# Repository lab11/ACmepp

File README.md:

AC Power Meters
===============

This repository contains code and hardware for a set of AC power meters.

ACme++
------

ACme++ is an updated version of the [ACme](http://acme.eecs.berkeley.edu) device.
The major change is a switch from the Epic platform (MSP430F1611 and CC2420) to
the CC2538 system on chip. Other changes include putting the relay on the phase
wire (instead of neutral) and a smaller AC-DC power supply.

While ACme++ is a wireless power meter in its own right, it was designed to be 
a prototype for the ultra-space-constrained PowerCube device.

PowerCube
---------

PowerCube is a one cubic inch power meter. It is designed to unobtrusively fit
on a power strip. This requires using six PCBs arranged in a cube with very
strategically placed components.

Software
--------

Software for the ACme++ is written on top of ContikiOS.

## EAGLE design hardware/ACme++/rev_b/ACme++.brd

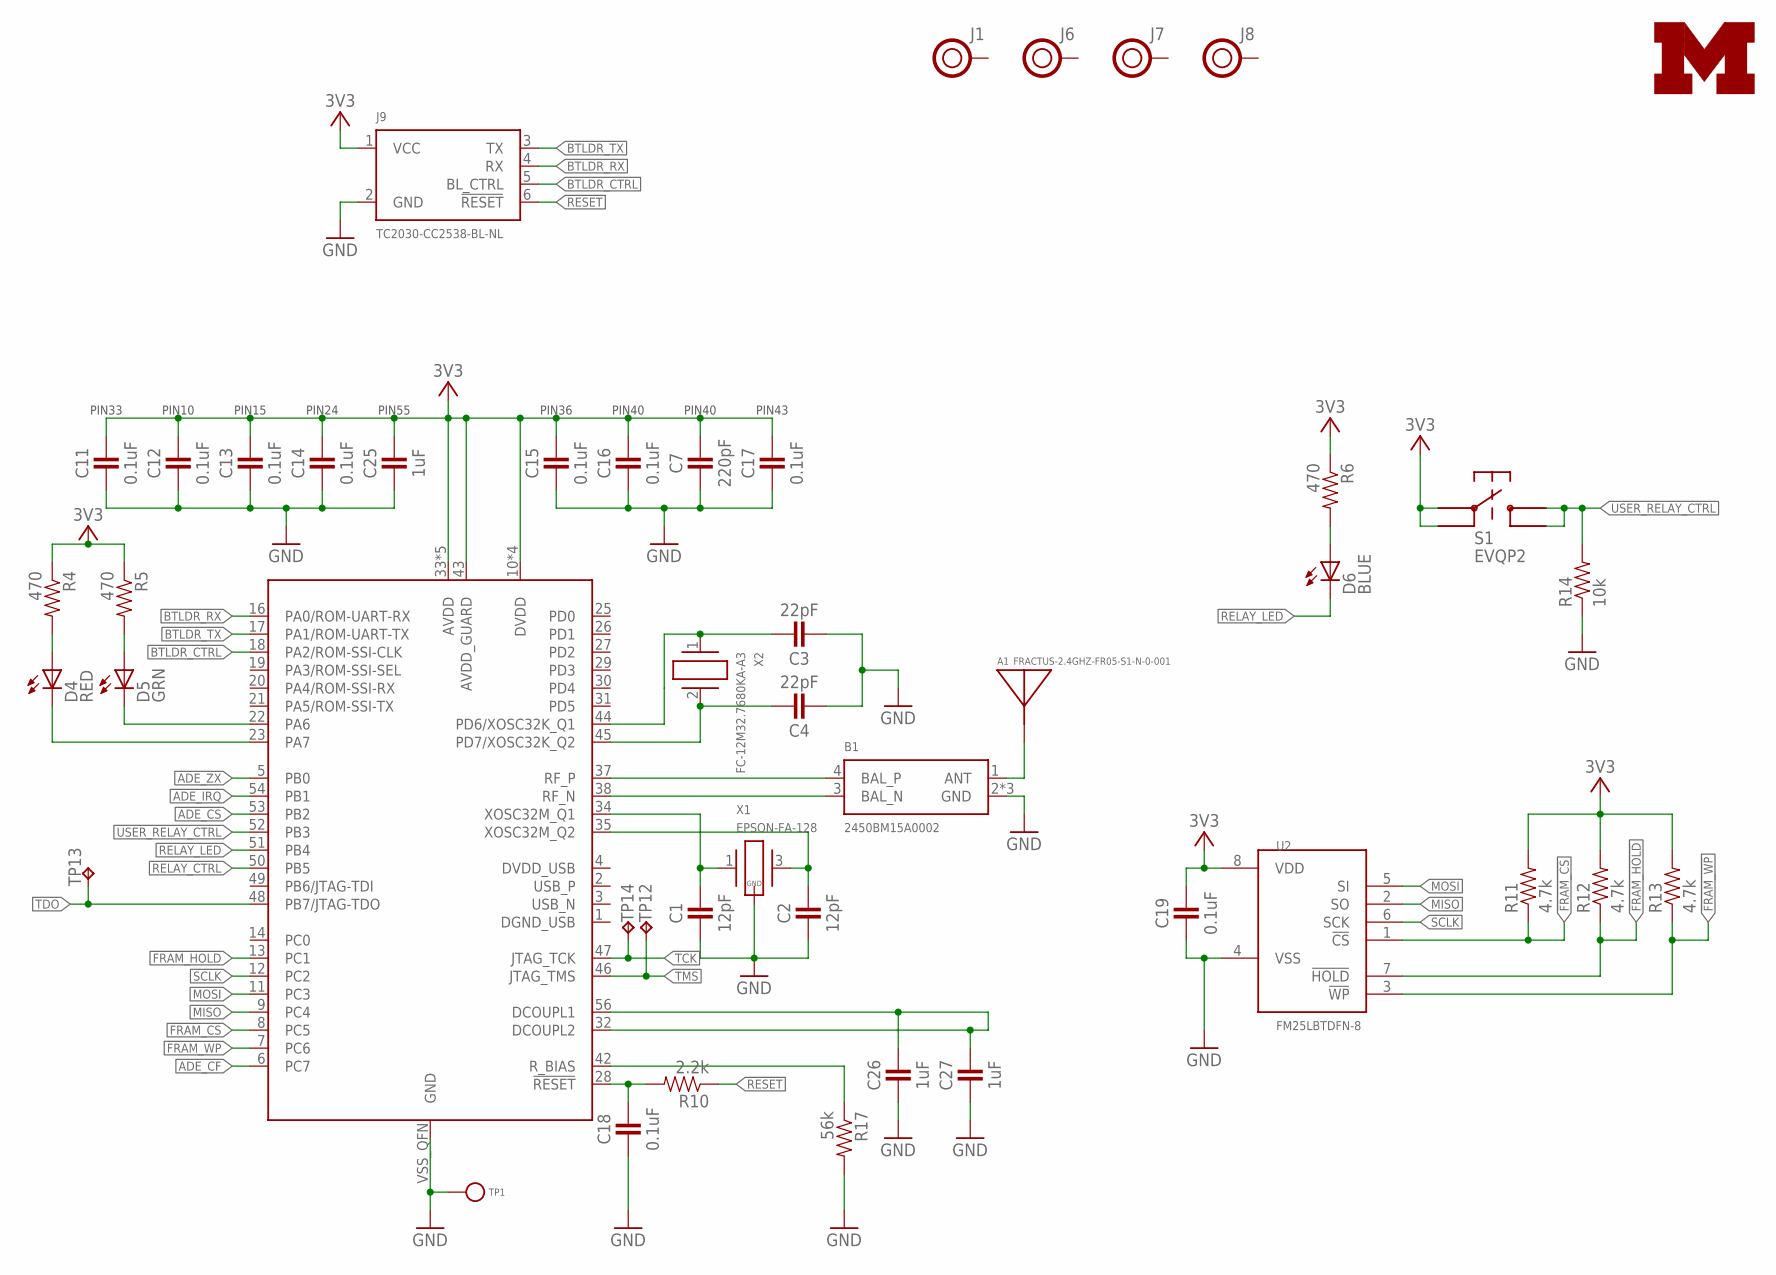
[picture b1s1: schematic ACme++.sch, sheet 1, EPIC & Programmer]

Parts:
A1: FRACTUS-2.4GHZ-FR05-S1-N-0-001; FRACTUS-ANTENNA-FR05-S1-N-0-001
B1: 2450BM15A0002; 2450BM
C1, C2: 12pF; 0402_CAP; DIGIKEY 445-1236-1-ND
C3, C4: 22pF; 0402_CAP; DIGIKEY 490-5868-1-ND
C7: 220pF; 0402_CAP; DIGIKEY 445-1251-1-ND
C11, C12, C13, C14, C15, C16, C17, C18, C19: 0.1uF; 0402_CAP; DIGIKEY 445-1265-1-ND
C25, C26, C27: 1uF; 0402_CAP; DIGIKEY 445-4998-1-ND
D4: RED; LED-0603; DIGIKEY 160-1835-1-ND
D5: GRN; LED-0603; DIGIKEY 160-1834-1-ND
D6: BLUE; LED-0603; DIGIKEY 160-1837-1-ND
J1, J6, J7, J8: HOLE; HOLE-0.125
J9: TC2030-CC2538-BL-NL; TC2030-IDC-NL
R4, R5, R6: 470; 0402_RES; DIGIKEY RHM470BHCT-ND
R10: 2.2k; 0402_RES; DIGIKEY RHM2.2KCECT-ND
R11, R12, R13: 4.7k; 0402_RES; DIGIKEY RHM4.7KCECT-ND
R14: 10k; 0603-RES; DIGIKEY RHM10.0KCFCT-ND
R17: 56k; 0402_RES; DIGIKEY RHM56KBHCT-ND
S1: EVQP2; DIGIKEY P11084SCT-ND
TP1: TEST_POINT_0.040IN; TESTPOINT_0.040IN
TP12, TP13, TP14: TPTP09SQ; TP09SQ
U1: CC2538; S-PVQFN-N56
U2: FM25LBTDFN-8; TDFN-8; DIGIKEY FM25L04B-DGRA-ND
U$3: UMICH_SOLID_MEDIUM; UMICH_SOLID_200MIL
X1: EPSON-FA-128; FA-128; DIGIKEY SER3800CT-ND
X2: FC-12M32.7680KA-A3; FC-12M

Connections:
3V3: C7.1, C11.1, C12.1, C13.1, C14.1, C15.1, C16.1, C17.1, C19.1, C25.1, J9.1 (VCC), R4.1, R5.1, R6.1, R11.2, R12.2, R13.2, S1.P$1, S1.P$3, U1.10 (DVDD), U1.15 (DVDD), U1.24 (DVDD), U1.33 (AVDD), U1.36 (AVDD), U1.39 (AVDD), U1.40 (AVDD), U1.41 (AVDD), U1.43 (AVDD_GUARD), U1.55 (DVDD), U2.8 (VDD); also elsewhere on the board
!ADE_CS: U1.53 (PB2); also elsewhere on the board
!ADE_IRQ: U1.54 (PB1); also elsewhere on the board
!FRAM_CS: R11.1, U1.8 (PC5), U2.1 (!CS)
!FRAM_HOLD: R12.1, U1.13 (PC1), U2.7 (!HOLD)
!FRAM_WP: R13.1, U1.7 (PC6), U2.3 (!WP)
!RESET: J9.6 (!RESET), R10.1
ADE_CF: U1.6 (PC7); also elsewhere on the board
ADE_ZX: U1.5 (PB0); also elsewhere on the board
ANTENNA: A1.1, B1.1 (ANT)
BTLDR_CTRL: J9.5 (BL_CTRL), U1.18 (PA2/ROM-SSI-CLK)
BTLDR_RX: J9.4 (RX), U1.16 (PA0/ROM-UART-RX)
BTLDR_TX: J9.3 (TX), U1.17 (PA1/ROM-UART-TX)
GND: B1.2 (GND), B1.5 (GND), B1.6 (GND), C1.2, C2.2, C3.2, C4.2, C7.2, C11.2, C12.2, C13.2, C14.2, C15.2, C16.2, C17.2, C18.2, C19.2, C25.2, C26.2, C27.2, J9.2 (GND), R14.1, R17.2, TP1.TESTPOINT, U1.VSS_QFN (GND), U2.4 (VSS), X1.2 (GND), X1.4 (GND); also elsewhere on the board
GREEN_LED: D5.C, U1.22 (PA6)
MISO: U1.9 (PC4), U2.2 (SO); also elsewhere on the board
MOSI: U1.11 (PC3), U2.5 (SI); also elsewhere on the board
unnamed: C26.1, C27.1, U1.32 (DCOUPL2), U1.56 (DCOUPL1)
unnamed: C18.1, R10.2, U1.28 (!RESET)
unnamed: C4.1, U1.45 (PD7/XOSC32K_Q2), X2.2
unnamed: C3.1, U1.44 (PD6/XOSC32K_Q1), X2.1
unnamed: R17.1, U1.42 (R_BIAS)
unnamed: C1.1, U1.34 (XOSC32M_Q1), X1.1
unnamed: C2.1, U1.35 (XOSC32M_Q2), X1.3 (2)
unnamed: D6.A, R6.2
unnamed: D4.A, R4.2
unnamed: D5.A, R5.2
RED_LED: D4.C, U1.23 (PA7)
RELAY_CTRL: U1.50 (PB5); also elsewhere on the board
RELAY_LED: D6.C, U1.51 (PB4)
RF_N: B1.3 (BAL_N), U1.38 (RF_N)
RF_P: B1.4 (BAL_P), U1.37 (RF_P)
SCLK: U1.12 (PC2), U2.6 (SCK); also elsewhere on the board
TCK: TP14.TP, U1.47 (JTAG_TCK)
TDO: TP13.TP, U1.48 (PB7/JTAG-TDO)
TMS: TP12.TP, U1.46 (JTAG_TMS)
USER_RELAY_CTRL: R14.2, S1.P$2, S1.P$4, U1.52 (PB3)

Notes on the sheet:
PIN10
PIN15
PIN24
PIN55
PIN33
PIN36
PIN40
PIN43

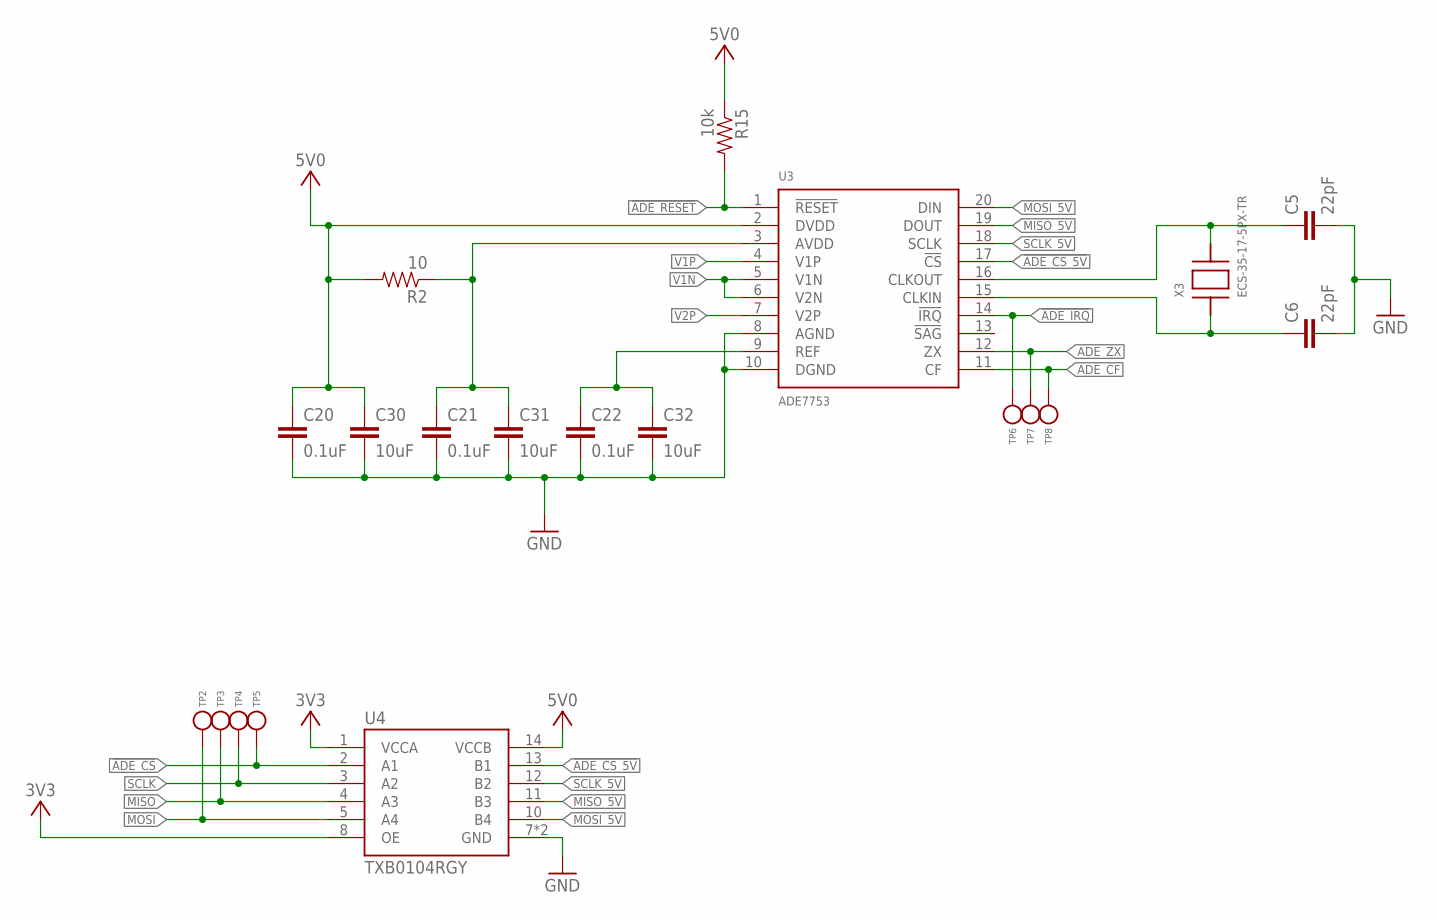
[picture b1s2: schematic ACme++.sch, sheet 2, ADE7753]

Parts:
C5, C6: 22pF; 0603-CAP; DIGIKEY 445-1273-1-ND
C20, C21, C22: 0.1uF; 0603-CAP; DIGIKEY 445-1316-1-ND
C30, C31, C32: 10uF; 0603-CAP; DIGIKEY 1276-1119-1-ND
R2: 10; 0603-RES; DIGIKEY RHM10.0CFCT-ND
R15: 10k; 0603-RES; DIGIKEY RHM10.0KCFCT-ND
TP2, TP3, TP4, TP5, TP6, TP7, TP8: TEST_POINT_0.040IN; TESTPOINT_0.040IN
U3: ADE7753; SSOP-20; MOUSER 584-ADE7753ARSZR
U4: TXB0104RGY; S-PVQFN-N14
X3: ECS-35-17-5PX-TR; CSM-7X

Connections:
3V3: U4.1 (VCCA), U4.8 (OE); also elsewhere on the board
5V0: C20.1, C30.1, R2.2, R15.1, U3.2 (DVDD), U4.14 (VCCB); also elsewhere on the board
!ADE_CS: TP5.TESTPOINT, U4.2 (A1); also elsewhere on the board
!ADE_CS_5V: U3.17 (!CS), U4.13 (B1)
!ADE_IRQ: TP6.TESTPOINT, U3.14 (!IRQ); also elsewhere on the board
!ADE_RESET: R15.2, U3.1 (!RESET)
ADE_AVDD: C21.1, C31.1, R2.1, U3.3 (AVDD)
ADE_CF: TP8.TESTPOINT, U3.11 (CF); also elsewhere on the board
ADE_ZX: TP7.TESTPOINT, U3.12 (ZX); also elsewhere on the board
GND: C5.2, C6.2, C20.2, C21.2, C22.2, C30.2, C31.2, C32.2, U3.8 (AGND), U3.10 (DGND), U4.7 (GND), U4.THERMALPAD (GND); also elsewhere on the board
MISO: TP3.TESTPOINT, U4.4 (A3); also elsewhere on the board
MISO_5V: U3.19 (DOUT), U4.11 (B3)
MOSI: TP2.TESTPOINT, U4.5 (A4); also elsewhere on the board
MOSI_5V: U3.20 (DIN), U4.10 (B4)
unnamed: C6.1, U3.15 (CLKIN), X3.1
unnamed: C22.1, C32.1, U3.9 (REF)
unnamed: C5.1, U3.16 (CLKOUT), X3.2
SCLK: TP4.TESTPOINT, U4.3 (A2); also elsewhere on the board
SCLK_5V: U3.18 (SCLK), U4.12 (B2)
V1N: U3.5 (V1N), U3.6 (V2N); also elsewhere on the board
V1P: U3.4 (V1P); also elsewhere on the board
V2P: U3.7 (V2P); also elsewhere on the board

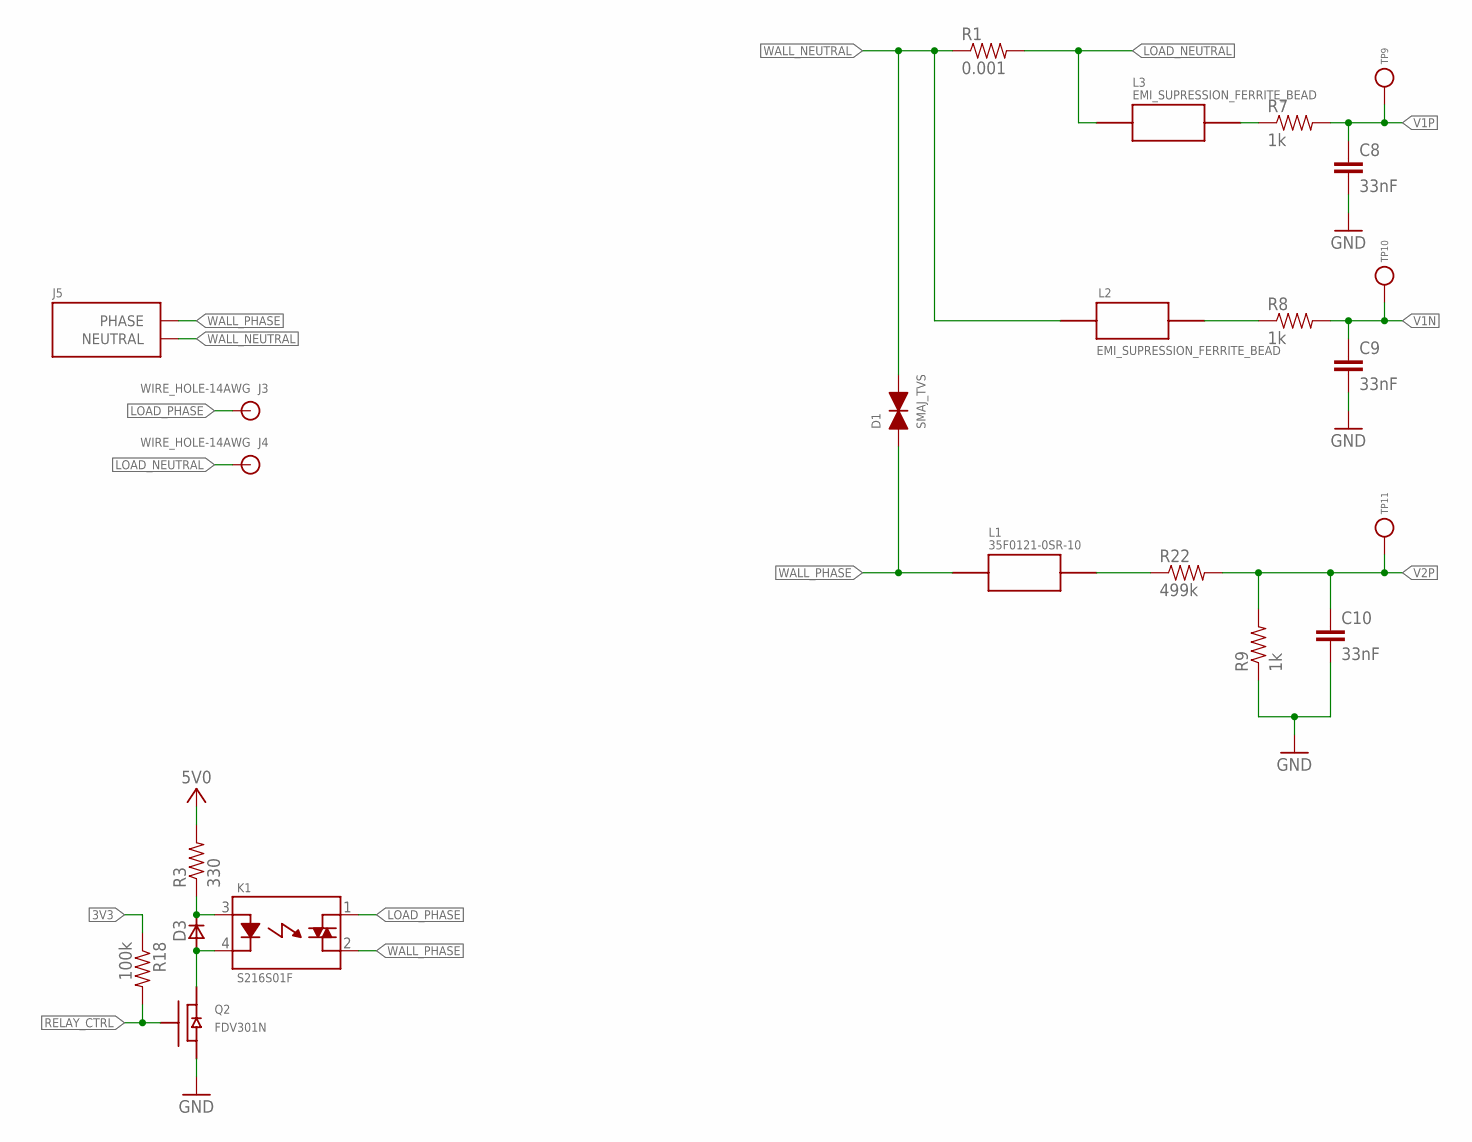
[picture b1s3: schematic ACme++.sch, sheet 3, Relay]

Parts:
C8, C9, C10: 33nF; 0805; DIGIKEY 478-1389-1-ND
D1: SMAJ_TVS; DO214_TVS
D3: DIODE_MMBD914; SOT-23
J3, J4: WIRE_HOLE-14AWG
J5: AC-PLUG-2; AC_MALE_PINS_2
K1: S216S01F; RELAY_SX16S0X
L1: 35F0121-0SR-10; 35F0102
L2, L3: EMI_SUPRESSION_FERRITE_BEAD; L1806
Q2: FDV301N; SOT-23
R1: 0.001; R2512; DIGIKEY P1.0TCT-ND
R3: 330; 0805; DIGIKEY RHM330KCT-ND
R7, R8, R9: 1k; 0805; DIGIKEY P16058CT-ND
R18: 100k; 0603-RES; DIGIKEY RHM100KCGCT-ND
R22: 499k; 0805; DIGIKEY P499KCCT-ND
TP9, TP10, TP11: TEST_POINT_0.040IN; TESTPOINT_0.040IN

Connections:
3V3: R18.1; also elsewhere on the board
5V0: R3.2; also elsewhere on the board
GND: C8.2, C9.2, C10.2, Q2.2 (S), R9.1; also elsewhere on the board
LOAD_NEUTRAL: J4.P$1, L3.P$1, R1.2
LOAD_PHASE: J3.P$1, K1.1
unnamed: D3.1 (ANNODE), K1.4, Q2.3 (D)
unnamed: D3.3 (CATHODE), K1.3, R3.1
unnamed: L2.P$2, R8.1
unnamed: L3.P$2, R7.1
unnamed: L1.2, R22.1
RELAY_CTRL: Q2.1 (G), R18.2; also elsewhere on the board
V1N: C9.1, R8.2, TP10.TESTPOINT; also elsewhere on the board
V1P: C8.1, R7.2, TP9.TESTPOINT; also elsewhere on the board
V2P: C10.1, R9.2, R22.2, TP11.TESTPOINT; also elsewhere on the board
WALL_NEUTRAL: D1.CATHODE, J5.NEUTRAL1 (NEUTRAL), J5.NEUTRAL2 (NEUTRAL), L2.P$1, R1.1; also elsewhere on the board
WALL_PHASE: D1.ANODE, J5.PHASE1 (PHASE), J5.PHASE2 (PHASE), K1.2, L1.1; also elsewhere on the board

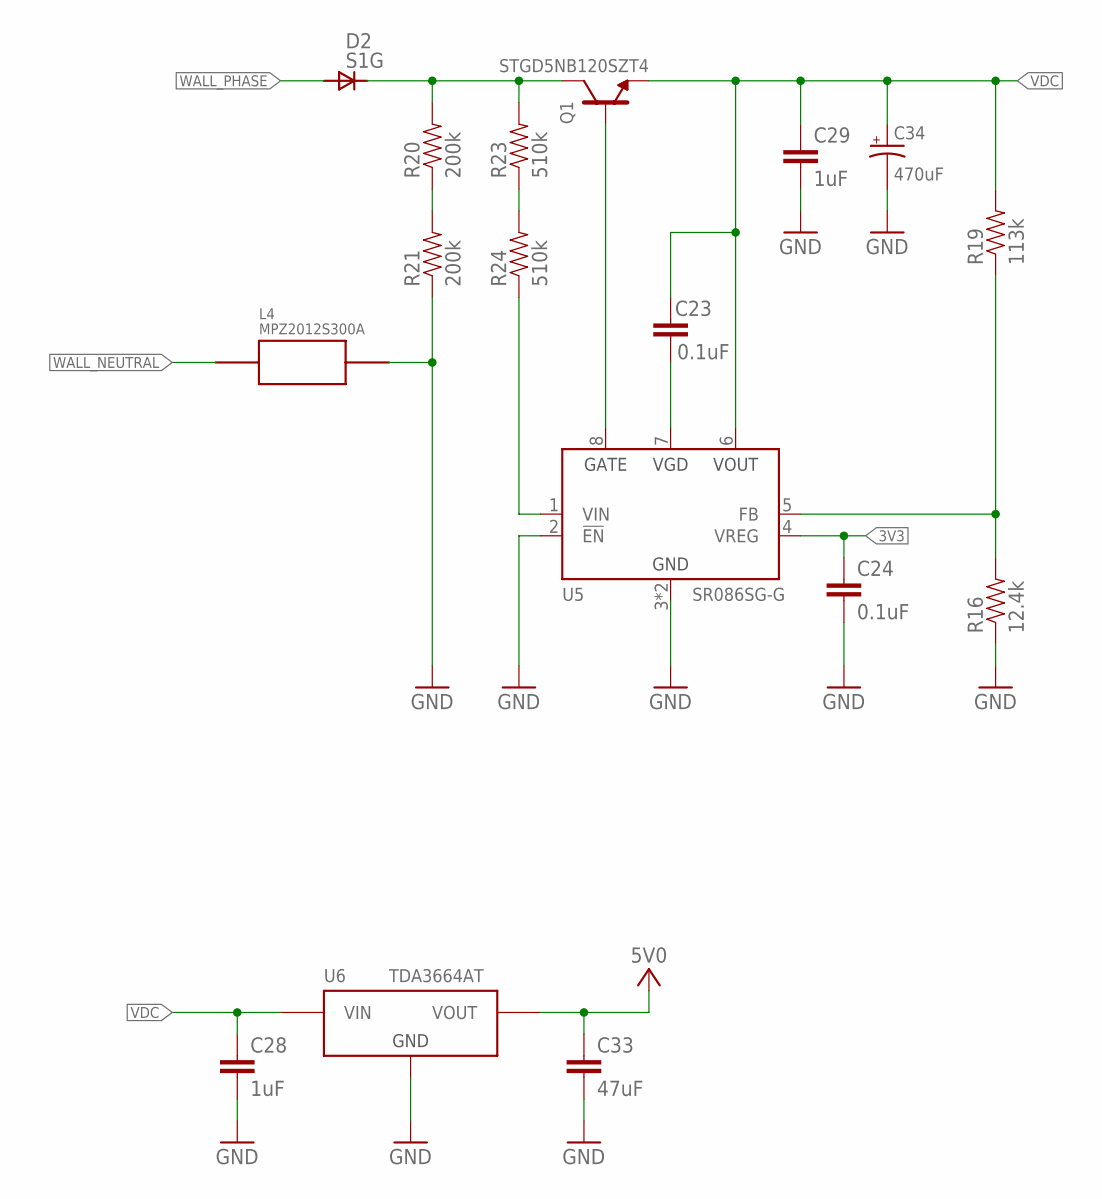
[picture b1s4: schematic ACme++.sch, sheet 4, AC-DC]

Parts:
C23, C24: 0.1uF; 0603-CAP; DIGIKEY 445-1316-1-ND
C28: 1uF; 0603-CAP; DIGIKEY 445-5956-1-ND
C29: 1uF; 1206; DIGIKEY 445-1381-1-ND
C33: 47uF; 1206; DIGIKEY 399-5508-1-ND
C34: 470uF; CAP_SM_10MM
D2: S1G; DO-214AC
L4: MPZ2012S300A; 0805_RESISTOR
Q1: STGD5NB120SZT4; DPAK
R16: 12.4k; 0603-RES; DIGIKEY RHM12.4KCFCT-ND
R19: 113k; 0603-RES; DIGIKEY RHM113KCFCT-ND
R20, R21: 200k; 1206; DIGIKEY P200KALCT-ND
R23, R24: 510k; 1206; DIGIKEY P510KALCT-ND
U5: SR086SG-G; SR086
U6: TDA3664AT; SOIC_8

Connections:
3V3: C24.1, U5.4 (VREG); also elsewhere on the board
5V0: C33.1, U6.1 (VOUT); also elsewhere on the board
DC_RECTIFIED: D2.CATHODE, Q1.P$2 (C), R20.2, R23.2
GND: C24.2, C28.2, C29.2, C33.2, C34.-, L4.P$2, R16.1, R21.1, U5.2 (!EN), U5.3 (GND), U5.PAD (GND), U6.3 (GND); also elsewhere on the board
unnamed: R20.1, R21.2
unnamed: R23.1, R24.2
unnamed: C23.2, U5.7 (VGD)
unnamed: R16.2, R19.1, U5.5 (FB)
SR086_GATE: Q1.P$1 (G), U5.8 (GATE)
SR086_VIN: R24.1, U5.1 (VIN)
VDC: C23.1, C28.1, C29.1, C34.+, Q1.P$3 (E), R19.2, U5.6 (VOUT), U6.8 (VIN)
WALL_NEUTRAL: L4.P$1; also elsewhere on the board
WALL_PHASE: D2.ANNODE; also elsewhere on the board

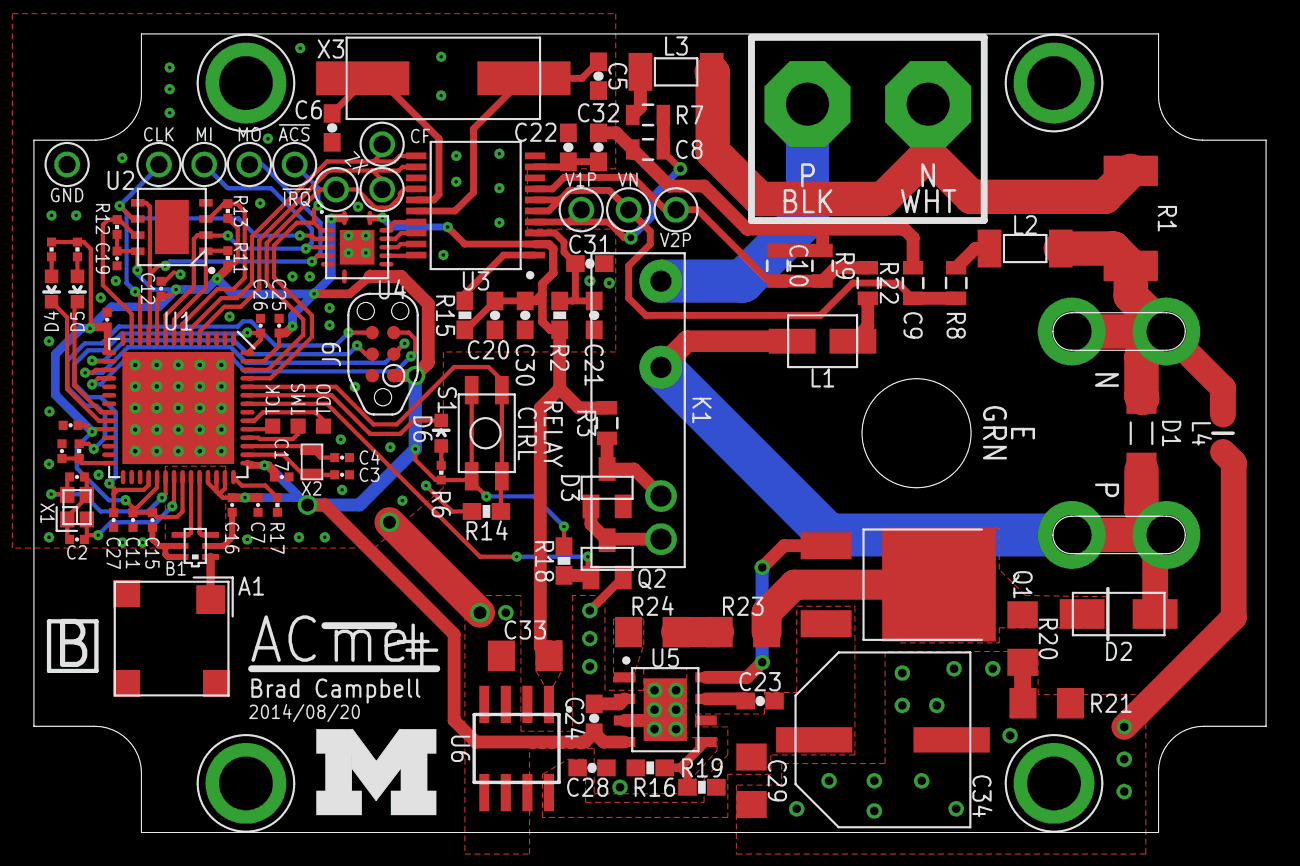
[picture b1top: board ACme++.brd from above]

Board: 2 copper layers, 72.6 x 47.1 mm, 106 parts (0 on the bottom side), 67 nets.

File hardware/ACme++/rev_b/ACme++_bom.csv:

# Bill of Materials
# Converted from ACme++_bom.xlsx
# Generated by bom_to_text.py

Qty,Value,Device,Package,Parts,Description,DIGIKEY,MOUSER,NEWARK,RICHARDSON_RFPD,McMASTER-CARR
1,FRACTUS-2.4GHZ-FR05-S1-N-0-001,FRACTUS-2.4GHZ-FR05-S1-N-0-001,FRACTUS-ANTENNA-FR05-S1-N-0-001,A1,Fractus Reach Xtend,,,,FR05-S1-N-0001B,
1,2450BM15A0002,2450BM15A0002,2450BM,B1,BALUN JTI MATCHED ZIGBEE,712-1536-1-ND,,,,
2,12pF,CAPACITOR,0402-CAP,"C1, C2",Capacitor,445-1236-1-ND,,,,
2,22pF,CAPACITOR,0402-CAP,"C3, C4",Capacitor,490-5868-1-ND,,,,
2,22pF,CAP0603-CAP,0603-CAP,"C5, C6",Capacitor,445-1273-1-ND,,,,
1,220pF,CAPACITOR,0402-CAP,C7,Capacitor,445-1251-1-ND,,,,
3,33nF,CAP0805,0805-CAP,"C8, C9, C10",Capacitor,478-1389-1-ND,,,,
9,0.1uF,CAPACITOR,0402-CAP,"C11, C12, C13, C14, C15, C16, C17, C18, C19",Capacitor,445-1265-1-ND,,,,
5,0.1uF,CAP0603-CAP,0603-CAP,"C20, C21, C22, C23, C24",Capacitor,445-1316-1-ND,,,,
3,1uF,CAPACITOR,0402-CAP,"C25, C26, C27",Capacitor,445-4998-1-ND,,,,
1,1uF,CAP0603-CAP,0603-CAP,C28,Capacitor,445-5956-1-ND,,,,
1,1uF,CAP1206,1206-CAP,C29,Capacitor,445-1381-1-ND,,,,
3,10uF,CAP0603-CAP,0603-CAP,"C30, C31, C32",Capacitor,1276-1119-1-ND,,,,
1,47uF,CAP1206,1206-CAP,C33,Capacitor,399-5508-1-ND,,,,
1,470uF,CAP_EEE-FP1E471AP,CAP_SM_10MM,C34,Surface mount low ESR cap.,PCE4440CT-ND,,,,
1,SMAJ_TVS,SMAJ_TVS,DO214_TVS,D1,,SMAJ250CALFCT-ND,,,,
1,S1G,S1G,DO-214AC,D2,Diode 400V 1A SMA,S1GFSCT-ND,,,,
1,DIODE_MMBD914,DIODE_MMBD914,SOT-23,D3,DIODE SML SIG 100V 0.2A SOT23-3,MMBD914FSCT-ND,,,,
1,RED,LED0603,LED-0603,D4,LEDs,160-1835-1-ND,,,,
1,GREEN,LED0603,LED-0603,D5,LEDs,160-1834-1-ND,,,,
1,BLUE,LED0603,LED-0603,D6,LEDs,160-1837-1-ND,,,,
1,S216S01F,S216S01F,RELAY_SX16S0X,K1,RELAY SSR 240VAC 16A TRIAC 4-SIP,425-2413-5-ND,852-S216S01F,14N9591,,
1,35F0121-0SR-10,35F0121-0SR-10,35F0102,L1,FERRITE 10A 42 OHMS @ 10 MHZ SMD,240-2520-1-ND,,,,
2,EMI_SUPRESSION_FERRITE_BEAD,EMI_SUPRESSION_FERRITE_BEAD,L1806,"L2, L3",FERRITE 300MA 150 OHM 1806 SMD,240-2418-1-ND,,,,
1,MPZ2012S300A,MPZ2012S300A,0805,L4,FERRITE CHIP 30 OHM 6A 0805,445-1566-1-ND,,,,
1,STGD5NB120SZT4,STGD5NB120SZT4,DPAK,Q1,5 A - 1200 V - low drop internally clamped IGBT,497-4352-1-ND,,,,
1,FDV301N,FDV301N,SOT-23,Q2,,FDV301NCT-ND,,,,
1,0.001,RESISTOR2512,R2512,R1,Resistor,P1.0TCT-ND,,,,
1,10,RESISTOR0603-RES,0603-RES,R2,Resistor,RHM10.0CFCT-ND,,,,
1,330,RESISTOR0805-RES,0805-RES,R3,Resistor,RHM330KCT-ND,,,,
3,470,RESISTOR,0402-RES,"R4, R5, R6",Resistor,RHM470BHCT-ND,,,,
3,1k,RESISTOR0805-RES,0805-RES,"R7, R8, R9",Resistor,P16058CT-ND,,,,
1,2.2k,RESISTOR,0402-RES,R10,Resistor,RHM2.2KCECT-ND,,,,
3,4.7k,RESISTOR,0402-RES,"R11, R12, R13",Resistor,RHM4.7KCECT-ND,,,,
2,10k,RESISTOR0603-RES,0603-RES,"R14, R15",Resistor,RHM10.0KCFCT-ND,,,,
1,12.4k,RESISTOR0603-RES,0603-RES,R16,Resistor,RHM12.4KCFCT-ND,,,,
1,56k,RESISTOR,0402-RES,R17,Resistor,RHM56KBHCT-ND,,,,
1,100k,RESISTOR0603-RES,0603-RES,R18,Resistor,RHM100KCGCT-ND,,,,
1,113k,RESISTOR0603-RES,0603-RES,R19,Resistor,RHM113KCFCT-ND,,,,
2,200k,RESISTOR1206,1206-RES,"R20, R21",Resistor,P200KALCT-ND,,,,
1,499k,RESISTOR0805-RES,0805-RES,R22,Resistor,P499KCCT-ND,,,,
2,510k,RESISTOR1206,1206-RES,"R23, R24",Resistor,P510KALCT-ND,,,,
1,EVQP2,EVQP2,EVQP2,S1,,P11084SCT-ND,,,,
1,TEST_POINT_0.040IN,TEST_POINT_0.040IN,TESTPOINT_0.040IN,TP1,0.040in Test Point Black,5001K-ND,,,,
3,TEST_POINT_0.040IN,TEST_POINT_0.040IN,TESTPOINT_0.040IN,"TP2, TP3, TP4",0.040in Test Point Blue,5117K-ND,,,,
1,TEST_POINT_0.040IN,TEST_POINT_0.040IN,TESTPOINT_0.040IN,TP5,0.040in Test Point Yellow,5004K-ND,,,,
3,TEST_POINT_0.040IN,TEST_POINT_0.040IN,TESTPOINT_0.040IN,"TP6, TP7, TP8",0.040in Test Point Green,5116K-ND,,,,
3,TEST_POINT_0.040IN,TEST_POINT_0.040IN,TESTPOINT_0.040IN,"TP9, TP10, TP11",0.040in Test Point Orange,5003K-ND,,,,
1,CC2538,CC2538,S-PVQFN-N56,U1,"A Powerful System-On-Chip for 2.4-GHz IEEE 802.15.4, 6LoWPAN",296-35797-1-ND,595-CC2538SF53RTQT,87W7713,,
1,FM25LBTDFN-8,FM25LBTDFN-8,TDFN-8,U2,IC FRAM 4KBIT 10MHZ 8SOIC,FM25L04B-DGRA-ND,877-FM25L04B-DG,,,
1,ADE7753,ADE7753,SSOP-20,U3,Single-Phase Multifunction Metering IC,ADE7753ARSZRLCT-ND,584-ADE7753ARSZR,59K0984,,
1,TXB0104RGY,TXB0104RGY,S-PVQFN-N14,U4,4-BIT BIDIRECTIONAL VOLTAGE-LEVEL TRANSLATOR,296-21930-1-ND,,,,
1,SR086SG-G,SR086SG-G,SR086,U5,Adjustable Off-Line Inductorless Switching Regulator,,689-SR086SG-G,,,
1,TDA3664AT,TDA3664AT,SOIC_8,U6,Very low dropout voltage/quiescent current 5 V voltage regulator,568-3310-1-ND,771-TDA3664ATN1118,,,
1,EPSON-FA-128,EPSON-FA-128,FA-128,X1,MHz RANGE CRYSTAL UNIT,SER3800CT-ND,732-FA128-32F20X-K3,,,
1,FC-12M32.7680KA-A3,FC-12M32.7680KA-A3,FC-12M,X2,kHz RANGE CRYSTAL UNIT,SER3672CT-ND,732-FC-12M-32.76KAA3,,,
1,ECS-35-17-5PX-TR,ECS-35-17-5PX-TR,CSM-7X,X3,CRYSTAL 3.579545MHZ 17PF SMD,XC1234CT-ND,520-CSM357-17-X,,,
1,ENCLOSURE,PPB-11860-BK,,,"BOX ABS 3.09X2.09X1.65"" BLK",377-1709-ND,,,,
0,ENCLOSURE,PPB-11860-WT,,,"BOX ABS 3.09X2.09X1.65"" WHT",377-1710-ND,,,,
1,SOCKET,739W-X2/03,,,OUTLET PWR NEMA 5-15R SNAPIN/IDC,Q228-ND,,,,
0,14AWG Black,6717 BK005,,,HOOK-UP STRND 14AWG BLACK 100',6717 BK005-ND,,,,
0,14AWG Green,6717 GR005,,,HOOK-UP STRND 14AWG GREEN 100',6717 GR005-ND,,,,
0,14AWG White,6717 WH005,,,HOOK-UP STRND 14AWG WHITE 100',6717 WH005-ND,,,,
4,#4 Screw,,,,"#4 3/16"" Panhead Self-Tapping Screws",,,,,92470a106

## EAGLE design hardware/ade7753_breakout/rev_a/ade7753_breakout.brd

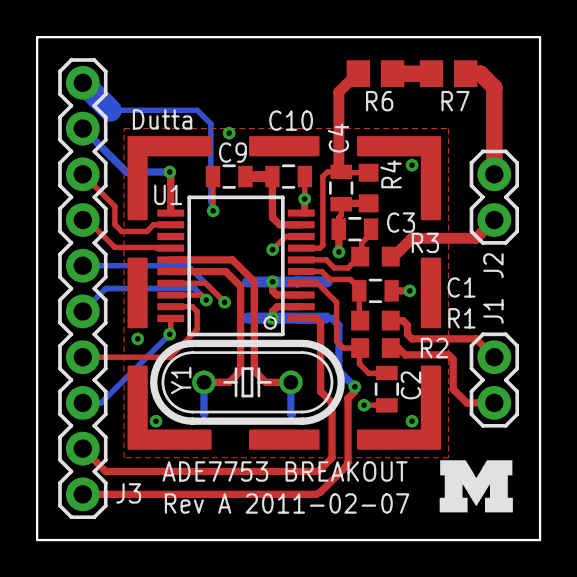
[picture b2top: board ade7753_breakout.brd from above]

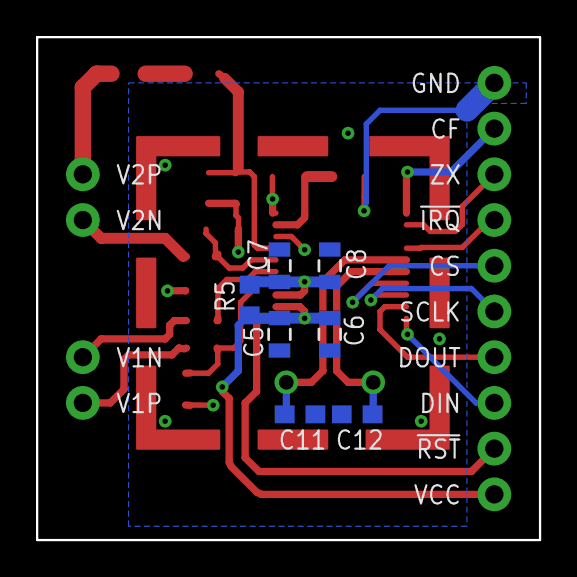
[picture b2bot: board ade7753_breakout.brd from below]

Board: 2 copper layers, 27.9 x 27.9 mm, 26 parts (7 on the bottom side), 23 nets.

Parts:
C1, C2, C3, C4: 33n; 0805
C5, C7, C9: 0.1u; 0805
C6, C8, C10: 10u; 0805
C11, C12: 22p; C0603
J1, J2: 1X02
J3: M10"; 1X10
R1, R2, R3, R4: 1k; R0603
R5: 10; R0603
R6, R7: 499k; R0805
U1: ADE7753; SSOP20
U$1: BLOCK-M
U$9: BMIS-202
Y1: 3.579 MHz; HC49/S

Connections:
GND: C1.2, C2.2, C3.2, C4.2, C5.2, C6.2, C7.2, C8.2, C9.2, C10.2, C11.2, C12.2, J3.10, R4.1, U1.8, U1.10
unnamed: J2.2, R7.1
unnamed: J1.1, R1.1
unnamed: J3.9, U1.11
unnamed: C4.1, R4.2, R6.2, U1.7
unnamed: C3.1, R3.2, U1.6
unnamed: C1.1, R1.2, U1.5
unnamed: R6.1, R7.2
unnamed: J1.2, R2.1
unnamed: J2.1, R3.1
unnamed: C2.1, R2.2, U1.4
unnamed: C9.1, C10.1, U1.9
unnamed: C11.1, U1.15, Y1.2
unnamed: C12.1, U1.16, Y1.1
unnamed: C7.1, C8.1, R5.1, U1.3
unnamed: C5.1, C6.1, J3.1, R5.2, U1.2
unnamed: J3.3, U1.20
unnamed: J3.4, U1.19
unnamed: J3.5, U1.18
unnamed: J3.6, U1.17
unnamed: J3.2, U1.1
unnamed: J3.7, U1.14
unnamed: J3.8, U1.12

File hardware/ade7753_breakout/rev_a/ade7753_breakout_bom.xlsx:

Part | Value | Device | Package | Description | Distributor | Quantity | Part# | Custom Part# | Price | min price break | Notes
C1, C2, C3, C4 | 33n | CAP0805 | C0805 | Capacitor | DigiKey | 4 | 478-3769-1-ND |  | 0.36299999999999999 | 100
C5, C7, C9 | 0.1u | CAP0805 | C0805 | Capacitor | DigiKey | 3 | 478-5721-1-ND |  | 0.20899999999999999 | 100
C6, C8, C10 | 10u | CAP0805 | C0805 | Capacitor | DigiKey | 3 | 478-5165-1-ND |  | 0.33 | 100
C11, C12 | 22p | C-USC0603 | C0603 | CAPACITOR, America | DigiKey | 2 | 478-5771-1-ND |  | 0.66 | 100
J1, J2 |  | M02PTH | 1X02 | Header 2 | DigiKey | 2 | A31112-ND |  | 0.2 | 25
J3 | M10" | M10" | 1X10 | Header 10 | DigiKey | 1 | A30844-ND |  | 0.54 | 25
R1, R2, R3, R4 | 1k | R-US_R0603 | R0603 | RESISTOR, American | DigiKey | 4 | RG16P1.0KBCT-ND |  | 0.40899999999999997 | 50
R5 | 10 | R-US_R0603 | R0603 | RESISTOR, American | DigiKey | 1 | CRT0603-BY-10R0ELFCT-ND |  | 0.25 | 10
R6, R7 | 499k | R-US_R0805 | R0805 | RESISTOR, American | DigiKey | 2 | RG20P499KBCT-ND |  | 0.40899999999999997 | 100
U1 | ADE7753 | ADE7753 | SSOP20 |  | DigiKey | 1 | ADE7753ARSZ-ND |  | 4.3099999999999996 | 25
Y1 | 3.579 MHz | CRYSTALHC49S | HC49/S | CRYSTAL | DigiKey | 1 | 887-1000-ND |  | 0.46 | 100

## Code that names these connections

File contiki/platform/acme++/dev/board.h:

/** \addtogroup cc2538
 * @{
 *
 * \defgroup acme++
 *
 * \note   Do not include this file directly. It gets included by contiki-conf
 *         after all relevant directives have been set.
 */
#ifndef BOARD_H_
#define BOARD_H_

#include "dev/gpio.h"
#include "dev/nvic.h"
/*---------------------------------------------------------------------------*/
/** \name SmartRF LED configuration
 *
 * LEDs on the SmartRF06 (EB and BB) are connected as follows:
 * - LED1 (Red)    -> PC0
 * - LED2 (Yellow) -> PC1
 * - LED3 (Green)  -> PC2
 * - LED4 (Orange) -> PC3
 *
 * LED1 shares the same pin with the USB pullup
 * @{
 */
/*---------------------------------------------------------------------------*/
/* Some files include leds.h before us, so we need to get rid of defaults in
 * leds.h before we provide correct definitions */
#undef LEDS_GREEN
#undef LEDS_YELLOW
#undef LEDS_RED
#undef LEDS_CONF_ALL

#define LEDS_BLUE                16 /**< PB4 */
#define LEDS_RED                 64 /**< PA6 */
#define LEDS_GREEN               128 /**< PA7 */
#define LEDS_CONF_ALL            208

/* Notify various examples that we have LEDs */
#define PLATFORM_HAS_LEDS        1

#define LED_BLUE_BASE            GPIO_B_BASE
#define LED_RED_BASE             GPIO_A_BASE
#define LED_GREEN_BASE           GPIO_A_BASE
#define LED_BLUE_MASK            GPIO_PIN_MASK(4)
#define LED_RED_MASK             GPIO_PIN_MASK(6)
#define LED_GREEN_MASK           GPIO_PIN_MASK(7)
/** @} */
/*---------------------------------------------------------------------------*/
/**
 * \name ADE7753 configuration
 *
 * These values configure which CC2538 pins to use for the ADE chip.
 * @{
 */
#define ADE7753_IRQ_N_PORT_NUM GPIO_B_NUM
#define ADE7753_IRQ_N_PIN      1
#define ADE7753_ZX_PORT_NUM    GPIO_B_NUM
#define ADE7753_ZX_PIN         0
#define ADE7753_CF_PORT_NUM    GPIO_C_NUM
#define ADE7753_CF_PIN         7
#define ADE7753_CS_N_PORT_NUM  GPIO_B_NUM
#define ADE7753_CS_N_PIN       2
/** @} */
/*---------------------------------------------------------------------------*/
/**
 * \name FM25LB configuration
 *
 * These values configure which CC2538 pins to use for the FRAM chip.
 * @{
 */
#define FM25LB_HOLD_N_PORT_NUM GPIO_C_NUM
#define FM25LB_HOLD_N_PIN      1
#define FM25LB_WP_N_PORT_NUM   GPIO_C_NUM
#define FM25LB_WP_N_PIN        6
#define FM25LB_CS_N_PORT_NUM   GPIO_C_NUM
#define FM25LB_CS_N_PIN        5
/** @} */
/*---------------------------------------------------------------------------*/
/**
 * \name SPI configuration
 *
 * These values configure which CC2538 pins to use for the SPI lines.
 * @{
 */
#define SPI_CLK_PORT  GPIO_C_NUM
#define SPI_CLK_PIN   2
#define SPI_MOSI_PORT GPIO_C_NUM
#define SPI_MOSI_PIN  3
#define SPI_MISO_PORT GPIO_C_NUM
#define SPI_MISO_PIN  4
/** @} */
/*---------------------------------------------------------------------------*/
/** \name GPIO
 *
 */
#define RELAY_CTRL_BASE          GPIO_B_BASE
#define RELAY_CTRL_MASK          GPIO_PIN_MASK(5)

#define RELAY_BUTTON_PORT        GPIO_B_NUM
#define RELAY_BUTTON_PIN         3
#define RELAY_BUTTON_VECTOR      NVIC_INT_GPIO_PORT_B
/** @} */
/*---------------------------------------------------------------------------*/
/** \name USB configuration
 *
 * The USB pullup is driven by PC0 and is shared with LED1
 */
#define USB_PULLUP_PORT          GPIO_C_BASE
#define USB_PULLUP_PIN           0
#define USB_PULLUP_PIN_MASK      (1 << USB_PULLUP_PIN)
/** @} */
/*---------------------------------------------------------------------------*/
/** \name UART configuration
 *
 * On the SmartRF06EB, the UART (XDS back channel) is connected to the
 * following ports/pins
 * - RX:  PA0
 * - TX:  PA1
 * - CTS: PB0 (Can only be used with UART1)
 * - RTS: PD3 (Can only be used with UART1)
 *
 * We configure the port to use UART0. To use UART1, replace UART0_* with
 * UART1_* below.
 * @{
 */
#define UART0_RX_PORT            GPIO_A_NUM
#define UART0_RX_PIN             0

#define UART0_TX_PORT            GPIO_A_NUM
#define UART0_TX_PIN             1
// unused uart1
#define UART1_CTS_PORT           GPIO_C_NUM
#define UART1_CTS_PIN            1

#define UART1_RTS_PORT           GPIO_C_NUM
#define UART1_RTS_PIN            2
/** @} */
/*---------------------------------------------------------------------------*/
/* Notify various examples that we do not have buttons */
#define PLATFORM_HAS_BUTTON      0
/** @} */
/*---------------------------------------------------------------------------*/
/**
 * \name Device string used on startup
 * @{
 */
#define BOARD_STRING "acme++"
/** @} */

#endif /* BOARD_H_ */

/**
 * @}
 * @}
 */

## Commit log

2013-12-19 start of acme++
2013-12-19 ignore eagle
2013-12-19 working on relay
2013-12-20 working on ac connections
2013-12-24 power supplies fleshed out
2013-12-24 should do this more than i do
2013-12-24 progress
    cleaned up schematic a bit
    initial arragnment on pcb
2013-12-24 added eval datasheet for the ac-dc
2013-12-24 working on routing
    power supply laid out
    working on ace
    lots of room...put cc2538 on this board? hard to argue not to...
2013-12-24 routing the cc2538
2013-12-25 working on ground plane
    man there are some rediculous traces for this cc2538
2013-12-25 routed.
    still not sure what to do with "GND" for the differential signals
    running to the ade
2013-12-25 routing and labeling
2013-12-26 added labels to schematic
2013-12-26 changed gnd and routed
    made the gnd for the ade measurement signals the emi filtered neutral
    from the wall. As best as I can tell this is was acme does. Updated that
    on the schematic and routed it.
2013-12-26 added regulator datasheet
2013-12-26 thinking about ac lines, tantalum caps
2013-12-26 routed ac under board, renamed
    did my thing where part numbers correspond to values
2013-12-26 added bom
2013-12-26 renamed bom
2013-12-26 routed the new sparkfun resistors
    I changed over to all sparkfun so had to swap out some parts
2013-12-26 updated bom
2013-12-26 added to gitignore
2013-12-26 more clearance for phase
2013-12-26 moved rev letter
2013-12-26 clean silkscreen
2013-12-27 more bom cleaning
2013-12-27 added non pcb items to bom
2013-12-27 added new layers
    These layers are for names (top and bot) that should be there for
    assembly but shouldn't be on the board (ie they just dont fit).
    Moved everthing that was on Reference to tNamesHiddem
2013-12-27 added pdf and info file
2014-01-03 moved prabal's ade breakout
    Still trying to get rid of that dropbox eagle folder.
2014-01-03 updates to acme++
    - no plated earth gnd
    - added test points
2014-01-03 more documentation of acme++
2014-01-03 moved relay back
2014-01-05 worked on plated cutouts...
    I hope sunstone will do something reasonable
2014-01-06 added ade files
2014-01-06 ade7753 structure written
2014-01-06 added headers to ade files and addded registers
2014-01-06 added ade mode reg values
2014-01-06 added interrupt register values
2014-01-06 updated register names
2014-01-06 init ade mode
2014-01-06 added ade test program
2014-01-06 broke up write to mode reg into bytes
2014-01-06 added VERY simple test program for ade
2014-01-07 moved phase trace
2014-01-07 changing 14awg holes
2014-01-07 octogons
2014-01-07 moved silkscreen
2014-01-07 more documentation for acme++
2014-01-07 formatting bom, added test points
2014-01-08 fabbing acme++ rev a
2014-01-08 update description
2014-01-15 moved ade files into dev
2014-01-15 copied platform files from sehnsor
2014-01-15 added app files for ade test app
2014-01-15 changed makefile to correct level for contiki
2014-01-15 renamed app folder
2014-01-17 acme photo
2014-01-26 contiki compiles now
2014-01-26 new acme++ doc
2014-01-27 new app, updated code for acme++ platform
2014-01-27 button works
2014-01-27 longer time between packets
2014-01-27 gitignore
2014-01-29 added led toggle and timer to ade test code
2014-01-29 switched msb and lsb in ade mode write
2014-01-29 removed redundant call to ade init
2014-02-12 fixed messageLen issue in adeReadReg
2014-02-12 added read calls to verify ade working
2014-02-24 updated contiki makefile for acme++
    uses new changes in contiki source
2014-02-24 moved headers for cc2538
2014-02-24 updated with contiki
2014-02-24 new app that is just a wireless switch
2014-02-26 changed platform name to acme++
    updated comments that were old
2014-02-26 updated acme++ platform to new contiki
2014-02-26 fixed leds
    they were backwards before (on was off)
2014-02-26 updated app a tad
2014-03-05 add more description to readme
2014-03-06 added more compiled output to gitignore
2014-03-06 updated acme_switch app to work with borderrouter
    corrected udp calls
    need my changes to contiki
2014-03-06 updated acme++ platform to new second addr style
2014-03-07 added memory for power state
    stored in fram
2014-03-07 enable bootloader
2014-03-18 Updated FRAM driver
    Now uses better spi driver and has a lot less crap in it
2014-03-18 ade chip coming along
2014-03-18 updates to contiki conf and main
2014-03-18 zeroes app for getting zero crossing
2014-03-19 ade test subscribes to new contiki formats
2014-03-19 added energy reads to ade test program
2014-03-27 updates to powercube
2014-03-28 transmit timing info
2014-05-21 updates to voltage virtualization app
2014-05-21 renamed zeros to gemini_voltage
2014-05-21 added app that can be used on 2538evm
2014-06-06 Updated files to conform with contiki dev changes
2014-06-08 acme app working with current contiki
2014-06-08 quick script to turn on and off
2014-08-13 updated acme++
    - removed ds2411
    - updated programmer to bootloader based version
    - moved leds
    - add holes with metal
2014-08-20 acme ++ rev b changes
2014-08-29 new version of acme++
2014-09-10 updated acme++ platform so bootloader works
2014-12-21 start on acme coap app
2014-12-21 acme switch with coap!
2014-12-21 added python script for acme++ coap
2014-12-21 added failsafe app
    turns acme++ back on
2014-12-21 updated platform to match contiki
2014-12-21 stop sending packets
2014-12-21 updated gitignore
2014-12-21 acme++ rev b
2014-12-24 many coap updates
2015-03-26 adding control to coap app
2015-05-09 state change notification

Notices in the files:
parts and their libraries:
SparkFun-Passives: Licensing: CC v3.0 Share-Alike You are welcome to use this library for commercial purposes.
